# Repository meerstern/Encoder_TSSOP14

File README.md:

# Encoder_TSSOP14

The Encoder Converter board of Kicad Files for AMS AS5048A, AS5047D and others with SPI interface.

[AMS社製磁気エンコーダ](http://ams.com/eng/Products/Magnetic-Position-Sensors)　AS5048A, AS5047D等のTSSOP14を2.54mmピッチへ変換するKicadファイルです。

3.3V電源及びSPIインタフェースのピンが出ています。
他のピンは基板上のパット及びチップ抵抗のパターンからアクセス可能です。

## AS5048A/AS5047D仕様

- 14bit(16384)/1回転の高分解能磁気エンコーダ変換基板です
- 磁石の向きをSPI通信を介して位置を読み取ることができます
- サンプリング周期は最大12kHzで値が更新されます
- ネオジム磁石とチップは5mm程度の距離でもある程度正確に読込できます
- 磁石中心とチップ中心を高精度に軸合わせしなくともある程度正確に読込できます

## 変換基板仕様

- 3.3V電源(5Vpinと3.3Vpinが基板上で短絡)
- サイズ20mm x 15mm
- M3 x2 ピッチ15mm固定穴
- SPI端子出力ピンのみ

## 寸法図

## 使用可能エンコーダ

- AS5048A [Digikey Link](http://www.digikey.jp/product-detail/ja/ams/AS5048A-HTSP-500/AS5048A-HTSP-500CT-ND/3188617)
- AS4047D [Digikey Link](http://www.digikey.jp/product-detail/ja/ams/AS5047D-ATSM/AS5047D-ATSMCT-ND/4895563)
- AS5047P [Digikey Link](http://www.digikey.jp/product-detail/ja/ams/AS5047P-ATSM/AS5047P-ATSMCT-ND/5287312)
※上記の全チップで動作確認している訳ではありません。

## 使用例

- ネオジム磁石をタイヤや歯車等の軸中心の可動部に取り付けます
- エンコーダ基板のチップをネオジム磁石の中心と合わせて台車等の固定部に取り付けます
- 下記は[ProjectinBall](http://projectionball.jp/)での使用例です。ミラー部にネオジム磁石、基板部にエンコーダ変換基板が取り付けてあります

## # プログラム例

### AS5048A SPI (Microchip C30)

※MOSIは常にhighのため、MOSIを3.3Vへ接続し、3線通信でも可。

```c
int data0,data1,res;
SPICS1_OFF;
putcSPI2(0xFF);
while(SPI2STATbits.SPITBF);
while(!SPI2STATbits.SPIRBF);
data0=getcSPI2()&0xFF;
putcSPI2(0xFF);
while(SPI2STATbits.SPITBF);
while(!SPI2STATbits.SPIRBF);
data1=getcSPI2()&0xFF;
res=((data0<<8)+data1)&0x3FFF;
SPICS1_ON;
```

### AS5047D/P SPI (Microchip C30)

```c
int data0,data1,res;
SPICS1_OFF;
putcSPI2(0x3F);
while(SPI2STATbits.SPITBF);
while(!SPI2STATbits.SPIRBF);
data0=getcSPI2()&0xFF;
putcSPI2(0xFF);
while(SPI2STATbits.SPITBF);
while(!SPI2STATbits.SPIRBF);
data1=getcSPI2()&0xFF;
res=((data0<<8)+data1)&0x3FFF;
SPICS1_ON;
```

## 販売

- AS5048A実装済みの変換基板を専用ネオジム磁石付きで販売しています。[スイッチサイエンス](https://www.switch-science.com/catalog/3140/)

License - MIT

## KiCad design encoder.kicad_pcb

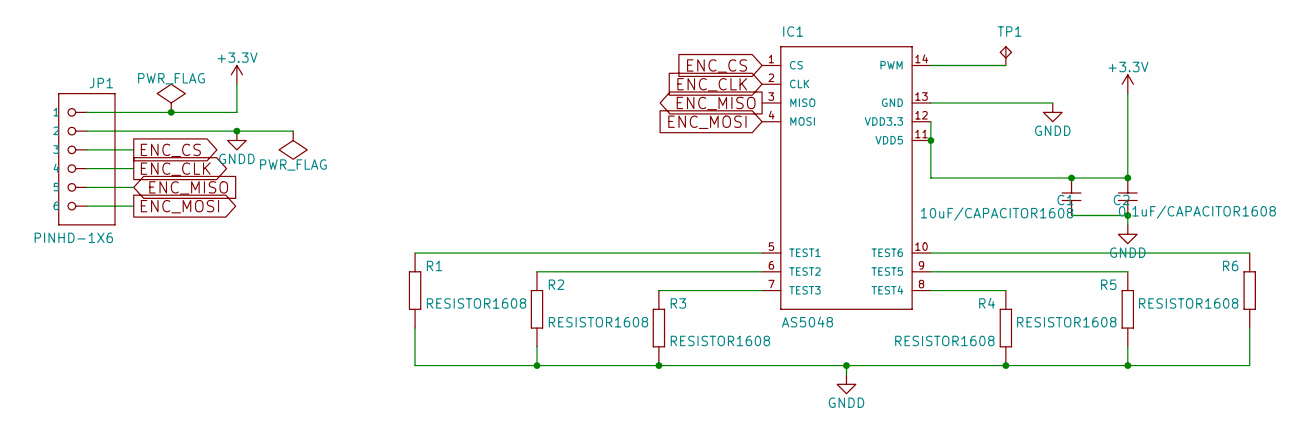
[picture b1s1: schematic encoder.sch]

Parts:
C1: 10uF/CAPACITOR1608; generic-SMD2012
C2: 0.1uF/CAPACITOR1608; generic-SMD1608
IC1: AS5048; ams5048a-TSSOP14
JP1: PINHD-1X6; pinhead-1X06
R1, R2, R3, R4, R5, R6: RESISTOR1608; generic-SMD1608
TP1: TPTP20SQ; testpad-TP10SQ

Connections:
+3V3: C1.1, C2.1, IC1.11 (VDD5), IC1.12 (VDD3.3), JP1.1
ENC_CLK: IC1.2 (CLK), JP1.4
ENC_CS: IC1.1 (CS), JP1.3
ENC_MISO: IC1.3 (MISO), JP1.5
ENC_MOSI: IC1.4 (MOSI), JP1.6
GNDD: C1.2, C2.2, IC1.13 (GND), JP1.2, R1.2, R2.2, R3.2, R4.2, R5.2, R6.2
unnamed: IC1.5 (TEST1), R1.1
unnamed: IC1.6 (TEST2), R2.1
unnamed: IC1.7 (TEST3), R3.1
unnamed: IC1.8 (TEST4), R4.1
unnamed: IC1.9 (TEST5), R5.1
unnamed: IC1.10 (TEST6), R6.1
unnamed: IC1.14 (PWM), TP1.TP

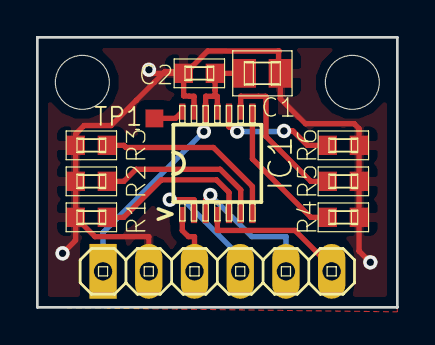
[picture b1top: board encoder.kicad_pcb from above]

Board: 2 copper layers, 20.0 x 15.0 mm, 11 parts (0 on the bottom side), 13 nets.

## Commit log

2017-01-22 Init
2017-05-28 Add panelized PCB data
2022-02-17 add dimensionalDrawing
2022-02-17 change readme
